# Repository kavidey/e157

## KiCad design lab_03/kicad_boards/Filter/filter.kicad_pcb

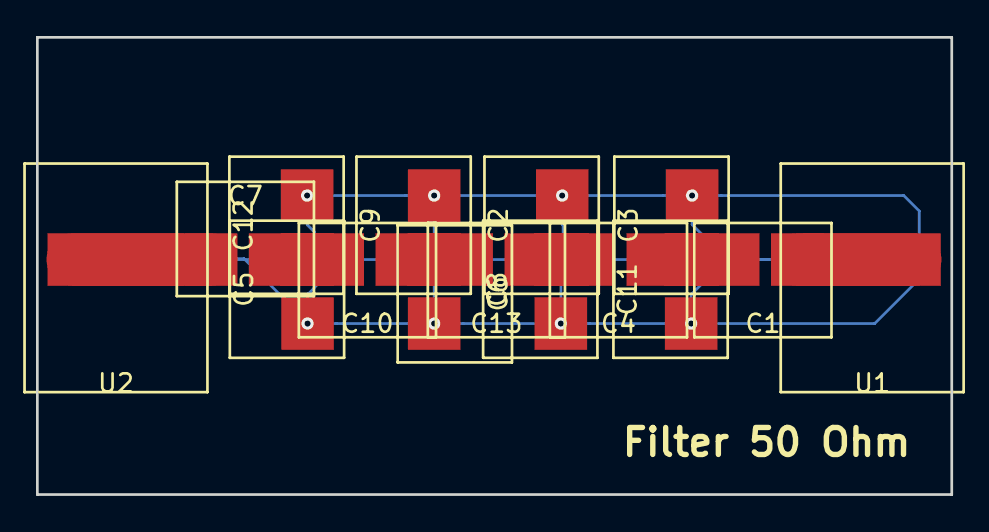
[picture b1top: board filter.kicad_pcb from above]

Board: 2 copper layers, 50.8 x 25.4 mm, 15 parts (0 on the bottom side), 11 nets.

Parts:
C1, C2, C3, C4, C5, C6, C7, C8, C9, C10, C11, C12, C13: C; filtercap
U1, U2: coax; rfcoax

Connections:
GND: C2.1, C3.1, C5.2, C6.1, C8.2, C9.1, C11.2, C12.1, U1.2, U2.2
unnamed: C1.1, C4.2
unnamed: C1.2, U1.1
unnamed: C2.2, C3.2
unnamed: C4.1, C7.2
unnamed: C5.1, C6.2
unnamed: C8.1, C9.2
unnamed: C10.1, C13.2
unnamed: C7.1, C10.2
unnamed: C11.1, C12.2
unnamed: C13.1, U2.1

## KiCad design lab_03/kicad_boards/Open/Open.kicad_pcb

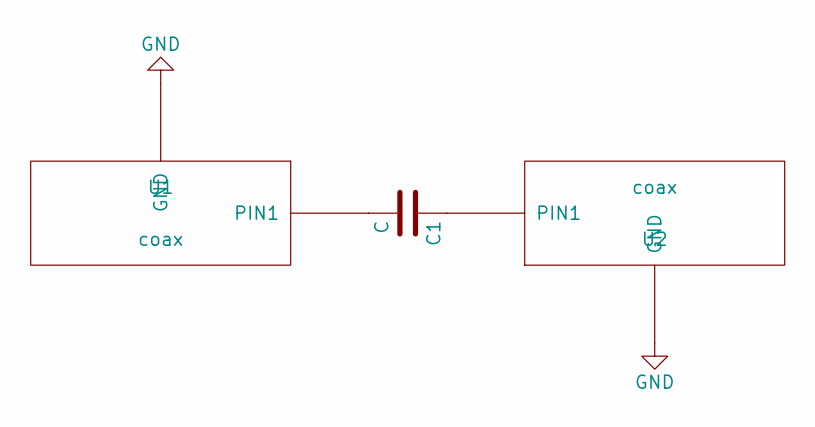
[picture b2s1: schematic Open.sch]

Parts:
C1: C; cap
U1, U2: coax; rfcoax

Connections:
GND: U1.2 (GND), U2.2 (GND)
unnamed: C1.1, U2.1 (PIN1)
unnamed: C1.2, U1.1 (PIN1)

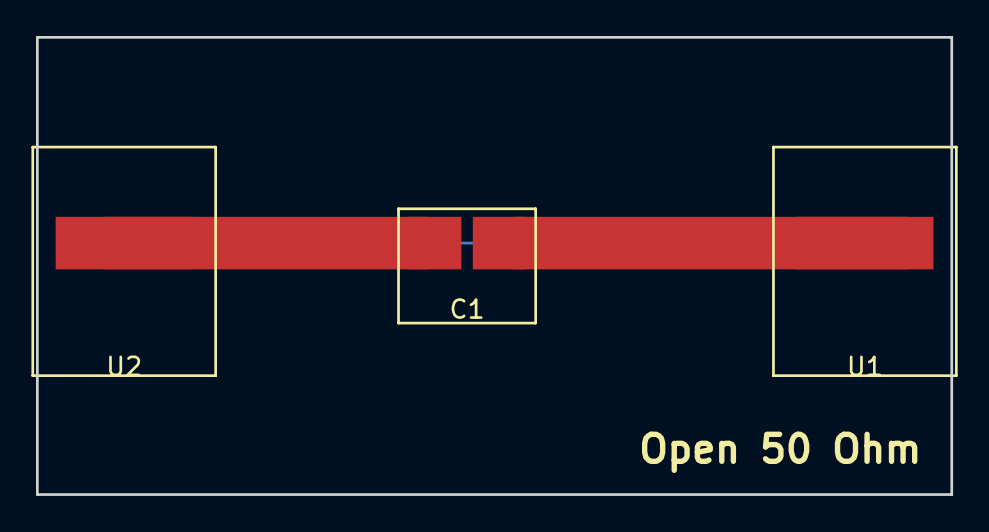
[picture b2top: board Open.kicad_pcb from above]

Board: 2 copper layers, 50.8 x 25.4 mm, 3 parts (0 on the bottom side), 3 nets.

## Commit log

2024-09-04 Add lab 1 schematics
2024-09-10 Add lab 2 data and p3 processing code
2024-09-23 Add all lab 2 files and scripts for lab 3
2024-09-24 Add data for main part of lab 1
2024-09-28 Add photos and update schematifcs
2024-09-28 Add missing photos
2024-09-29 Add additional simulations, processing scripts, and kicad files
2024-10-01 Add lab 3 extra credit
2024-10-03 Full data and sim for lab 3
2024-10-05 Add simulation code and schematics for DP1
2024-10-06 Add report, schematics, and code for DP1
2024-10-08 Add data from lab and fixed simulations
2024-10-08 Add additional data, clean up code
2024-10-10 Update sim with correct frequency
2024-10-10 Update report and add figures
2024-10-10 Add all code and figures for assembled filter
2024-10-10 Add phase plot and replace pngs with pdfs
2024-10-10 Add all sim figures
2024-10-10 Add analytical figures
2024-10-12 Finish DP1!
    Update code for plots and report
2024-10-12 Small grammar fixes
2024-11-13 Add all lab 4 files
2024-11-19 Data and code for day 1 of lab 2
2024-11-19 Data and code for day 2 of lab 5
2024-11-20 Add day 3 data for lab 5
2024-11-24 Add report
2024-11-24 Lab 6 extra credit code
2024-12-01 Add data and code for lab 6 day 1
2024-12-03 Add day 2 files
2024-12-07 add finished data and code for lab 6
2024-12-13 Add dp2 data files
2024-12-14 Part way done with DP2 report
2024-12-14 Rename files
2024-12-14 Finish DP2!!
